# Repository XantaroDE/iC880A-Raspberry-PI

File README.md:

# Raspberry PI + IMST iC880A Gateway Shield

Based on the idea of [ch2i][1], but complete rework.

This PCB is used to connect Raspberry PI and ISMT [iC880A][2] LoraWan concentrator Gateway (SPI version) togehter and to be able to put the whole thing into a outdoor enclosure. Power can be supplied via passive or active PoE adapters.

:warning: **Use at your own risk, always check your layout before manufacturing!**

## Features

 - highvoltage power regulator for passive PoE -48V usage based on LM2576
 - optional use DC/DC module for active PoE adapters with +12V output
 - BME280 header for temperature & humidity measurement within the housing, optional BMP280
 - DS18S20 Header for outside & inside/case sensor
 - added GPS module for time & PPS sync
 - optional +3V3 -> +5V TTL serial converter, could be used for other sensors like [SDS011][3] dust particle sensor 
 - LC filters on power supply rails
 - LED for GPS PPS and signal routed to GPIO25
 - DS1307 RTC hardware clock for Raspberry + Battery 

## Schematic

<br>
[PDF download](https://raw.githubusercontent.com/XantaroDE/iC880A-Raspberry-PI/master/pictures/RPI-Lora-Gateway-Shield.sch.pdf)

## Board

**Top side**

**Bottom side**

You can order the PCB of this board at [elecrow][4] with the supplied gerbers.

## License

This work is licensed under a [Creative Commons Attribution-NonCommercial 4.0 International License](http://creativecommons.org/licenses/by-nc/4.0/)    
If you want to do commercial stuff with this project, please contact [Xantaro Deutschland GmbH](https://www.xantaro.net) so we can organize an simple agreement.

[1]: https://github.com/ch2i/iC880A-Raspberry-PI/
[2]: http://webshop.imst.de/ic880a-spi-lorawan-concentrator-868mhz.html
[3]: https://luftdaten.info/
[4]: https://www.elecrow.com/pcb-manufacturing.html

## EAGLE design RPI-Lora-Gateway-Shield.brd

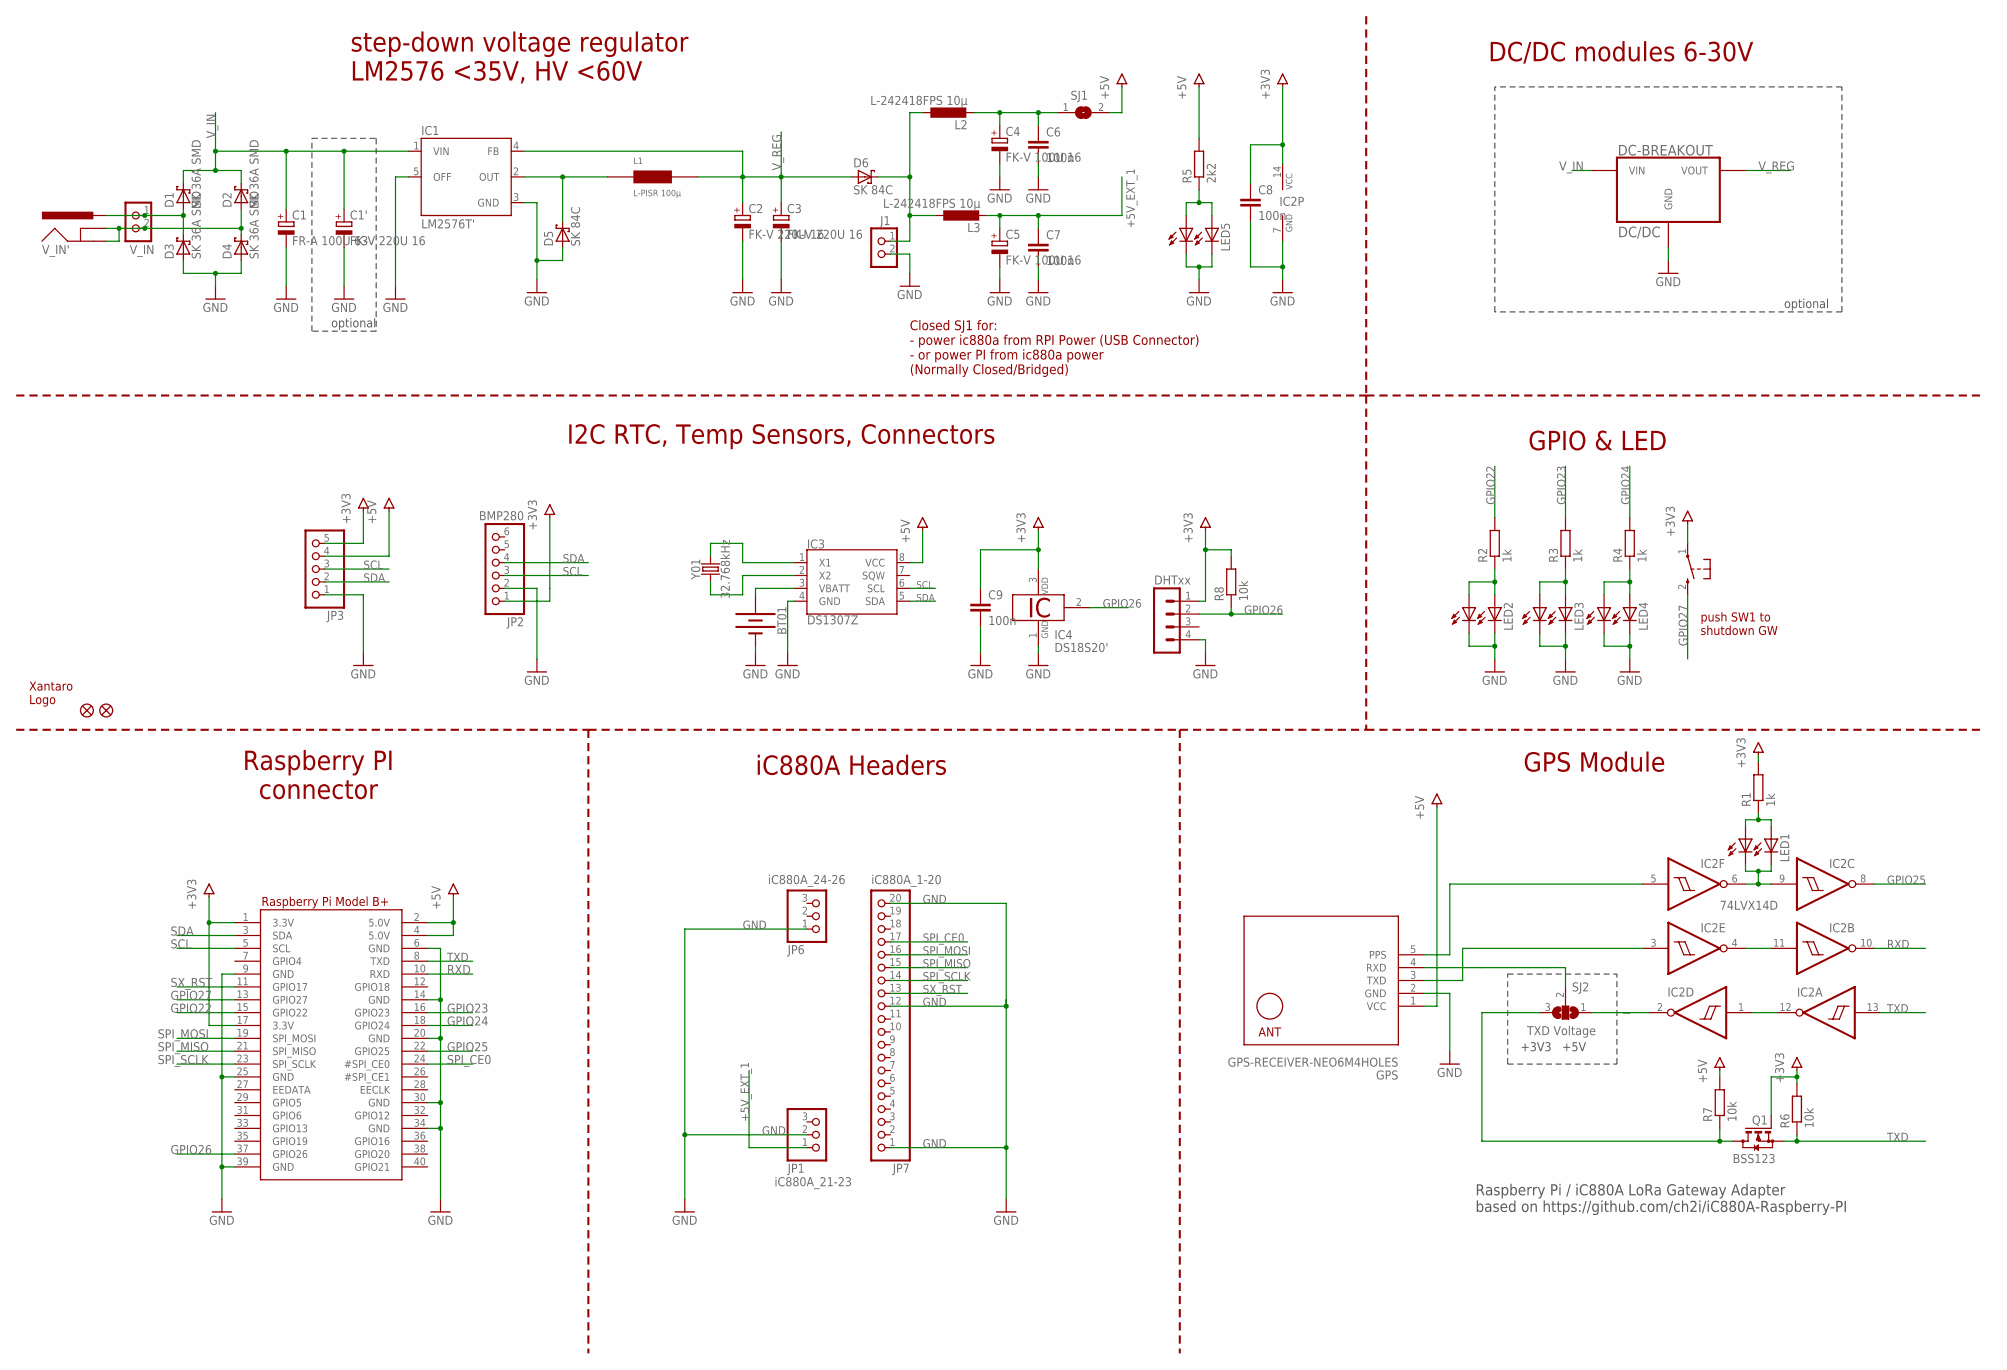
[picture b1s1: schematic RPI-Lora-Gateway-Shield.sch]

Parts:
BT01: BATTERY-12MM_PTH; BATTCON_12MM_PTH
C1: FR-A 100U 63; E3,5-8
C1', C2, C3: FK-V 220U 16; PANASONIC_E
C4, C5: FK-V 100U 16; PANASONIC_D
C6, C7, C8, C9: 100n; C0805
D1, D2, D3, D4: SK 36A SMD; SMB
D5, D6: SK 84C; SMC
DC/DC: DC-BREAKOUT
FID2, FID3: FIDUCIAL""; FIDUCIAL_1MM
GPS: GPS-RECEIVER-NEO6M4HOLES; GPS-RECEIVER-NEO6M_4HOLES
IC1: LM2576T'; TO220-5_90
IC2: 74LVX14D; SO14
IC3: DS1307Z; SO08-0.15
IC4: DS18S20'; TO92-2
J1: +5V_IN; TERMINAL_BLOCK_2P_5
J5: DHTxx; 1X04_NO_LOCK
JP1: iC880A_21-23; 1X03
JP2: BMP280; 1X06
JP3: PINHD-1X5; 1X05
JP6: iC880A_24-26; 1X03
JP7: iC880A_1-20; 1X20
L1: L-PISR 100µ; PISR
L2, L3: L-242418FPS 10µ; L5650M
LED1, LED2, LED3, LED4, LED5: LEDCHIPLED_0805; CHIPLED_0805
LED1', LED2', LED3', LED4', LED5': LED3MM
Q1: BSS123; SOT23
R1, R2, R3, R4: 1k; R0805
R5: 2k2; R0805
R6, R7, R8: 10k; R0805
RPI1: RASPBERRYPI_BPLUS_IDC; 2X20
SJ1: SJCLOSED; SJ_CLOSED
SJ2: TXD Voltage; SJ_2
SW1': RESET; KSS-2EG4430
U$4: XAN_LOGO_FULL_SILK_L; XAN_FULL_SILK_L
V_IN: V_IN; TERMINAL_BLOCK_2P_5
V_IN': POWER_JACKPTH; POWER_JACK_PTH
Y01: 32.768kHz; CRYSTAL-SMD-2X6-CYL

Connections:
+3V3: C8.1, C9.1, IC2.14 (VCC), IC4.3 (VDD), J5.1, JP2.1, JP3.5, Q1.1 (G), R1.2, R6.2, R8.2, RPI1.1 (3.3V), RPI1.17 (3.3V), SW1'.1
+5V: GPS.1 (VCC), IC3.8 (VCC), JP3.4, R5.2, R7.2, RPI1.2 (5.0V), RPI1.4 (5.0V), SJ1.2
+5V_EXT_1: C5.+, C7.1, JP1.1, L3.2
+5V_EXT_2: C4.+, C6.1, L2.2, SJ1.1
GND: BT01.2 (-), C1.-, C1'.-, C2.-, C3.-, C4.-, C5.-, C6.2, C7.2, C8.2, C9.2, D3.A, D4.A, D5.A, DC/DC.GND-1 (GND), DC/DC.GND-2 (GND), DC/DC.GND-3 (GND), DC/DC.GND-4 (GND), GPS.2 (GND), IC1.3 (GND), IC1.5 (OFF), IC2.7 (GND), IC3.4 (GND), IC4.1 (GND), J1.2, J5.4, JP1.2, JP2.2, JP3.1, JP6.1, JP7.1, JP7.12, JP7.20, LED2.C, LED2'.K (C), LED3.C, LED3'.K (C), LED4.C, LED4'.K (C), LED5.C, LED5'.K (C), RPI1.6 (GND), RPI1.9 (GND), RPI1.14 (GND), RPI1.20 (GND), RPI1.25 (GND), RPI1.30 (GND), RPI1.34 (GND), RPI1.39 (GND)
GPIO22: R2.2, RPI1.15 (GPIO22)
GPIO23: R3.2, RPI1.16 (GPIO23)
GPIO24: R4.2, RPI1.18 (GPIO24)
GPIO25: IC2.8 (O), RPI1.22 (GPIO25)
GPIO26: IC4.2 (1W), J5.2, R8.1, RPI1.37 (GPIO26)
GPIO27: RPI1.13 (GPIO27), SW1'.2 (S)
unnamed: D1.A, D3.C, V_IN.1, V_IN'.PWR
unnamed: LED1.A, LED1'.A, R1.1
unnamed: IC2.1 (I), IC2.12 (O)
unnamed: D6.C, J1.1, L2.1, L3.1
unnamed: D2.A, D4.C, V_IN.2, V_IN'.GND, V_IN'.GNDBREAK
unnamed: GPS.5 (PPS), IC2.5 (I)
unnamed: IC2.6 (O), IC2.9 (I), LED1.C, LED1'.K (C)
unnamed: GPS.3 (TXD), IC2.3 (I)
unnamed: IC2.4 (O), IC2.11 (I)
unnamed: GPS.4 (RXD), SJ2.2
unnamed: IC2.2 (O), SJ2.1
unnamed: D5.C, IC1.2 (OUT), L1.1
unnamed: BT01.1 (+), IC3.3 (VBATT)
unnamed: IC3.2 (X2), Y01.X1 (1)
unnamed: IC3.1 (X1), Y01.X2 (2)
unnamed: LED5.A, LED5'.A, R5.1
unnamed: LED3.A, LED3'.A, R3.1
unnamed: LED4.A, LED4'.A, R4.1
unnamed: Q1.3 (D), R7.1, SJ2.3
unnamed: LED2.A, LED2'.A, R2.1
RXD: IC2.10 (O), RPI1.10 (RXD)
SCL: IC3.6 (SCL), JP2.3, JP3.3, RPI1.5 (SCL)
SDA: IC3.5 (SDA), JP2.4, JP3.2, RPI1.3 (SDA)
SPI_CE0: JP7.17, RPI1.24 (#SPI_CE0)
SPI_MISO: JP7.15, RPI1.21 (SPI_MISO)
SPI_MOSI: JP7.16, RPI1.19 (SPI_MOSI)
SPI_SCLK: JP7.14, RPI1.23 (SPI_SCLK)
SX_RST: JP7.13, RPI1.11 (GPIO17)
TXD: IC2.13 (I), Q1.2 (S), R6.1, RPI1.8 (TXD)
V_IN: C1.+, C1'.+, D1.C, D2.C, DC/DC.VIN-1 (VIN), DC/DC.VIN-2 (VIN), IC1.1 (VIN)
V_REG: C2.+, C3.+, D6.A, DC/DC.VOUT-1 (VOUT), DC/DC.VOUT-2 (VOUT), IC1.4 (FB), L1.2

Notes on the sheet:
iC880A Headers
GPS Module
Raspberry PI connector
GPIO & LED
I2C RTC, Temp Sensors, Connectors
Closed SJ1 for: - power ic880a from RPI Power (USB Connector) - or power PI from ic880a power (Normally Closed/Bridged)
push SW1 to shutdown GW
step-down voltage regulator LM2576 <35V, HV <60V
DC/DC modules 6-30V
optional
+3V3 +5V
Raspberry Pi / iC880A LoRa Gateway Adapter based on https://github.com/ch2i/iC880A-Raspberry-PI

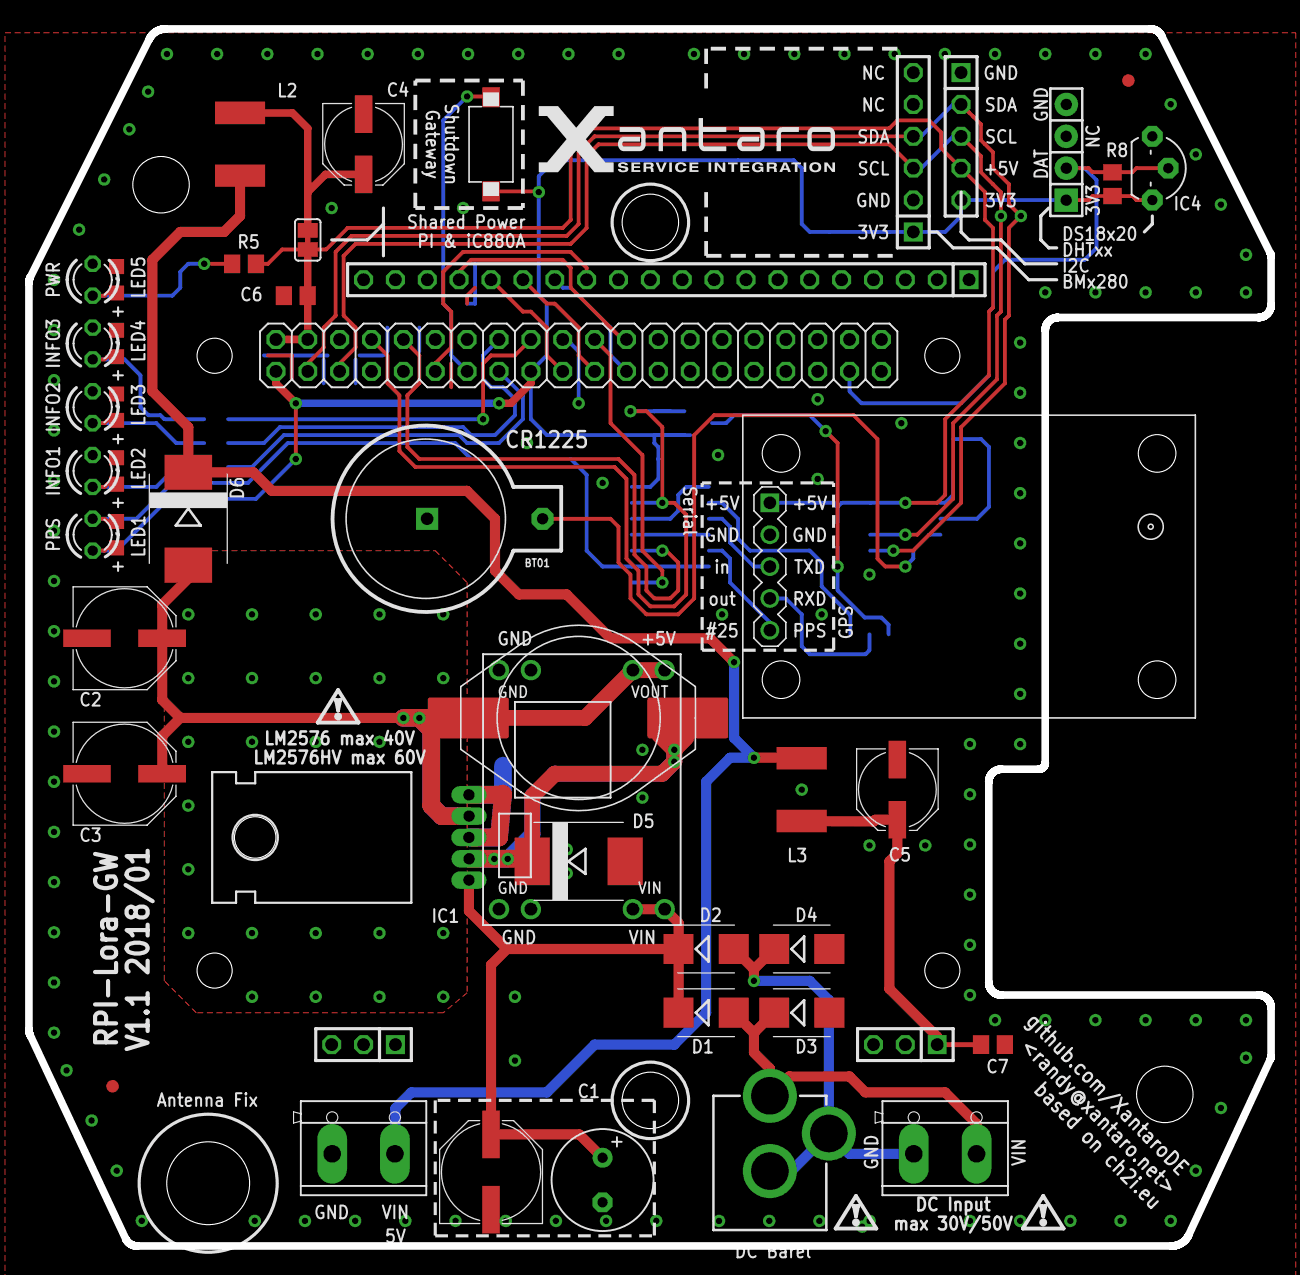
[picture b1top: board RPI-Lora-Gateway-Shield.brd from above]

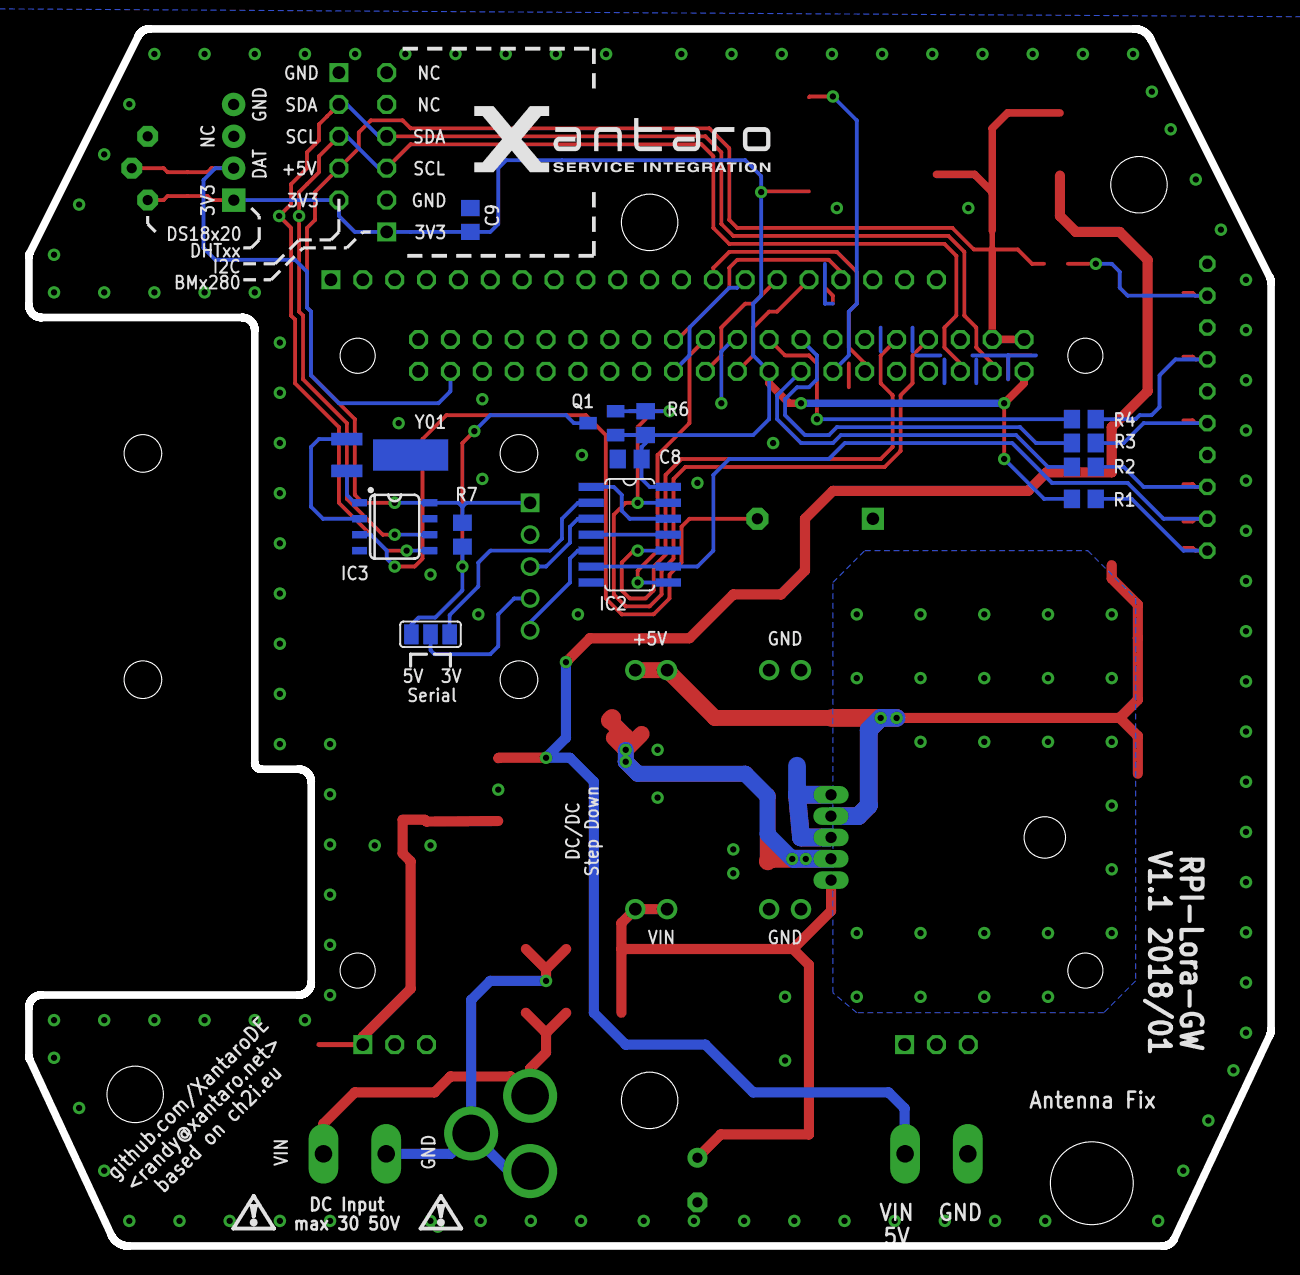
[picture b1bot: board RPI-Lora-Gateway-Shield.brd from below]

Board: 2 copper layers, 99.0 x 97.0 mm, 63 parts (14 on the bottom side), 42 nets.

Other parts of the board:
U$5: XAN_LOGO_FULL_SILK_L; XAN_FULL_SILK_L

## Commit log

2018-08-07 moved original files into ch2i-orig/
2018-08-07 push own version, schematics, gerber files...
2018-08-07 modified README
2018-08-07 typos

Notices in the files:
parts and their libraries:
microbuilder: This work is placed in the public domain, and may be freely used for commercial and non-commercial work with the following conditions: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
SparkFun-Connectors: Licensing: Creative Commons ShareAlike 4.0 International - https://creativecommons.org/licenses/by-sa/4.0
